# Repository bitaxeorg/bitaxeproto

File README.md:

bitaxeProto miner with quad Block Proto MC3 ASICs

It is still an untested prototype! Don't build this expecting it to work yet.

- [Open Hardware License](LICENSE); Real Open Source.
	- [KiCAD](https://kicad.org) design files. 
- Four Proto MC3 ASICs, two stacks of two ASICs
	- Each MC3 is nominally 1.12V with approx 675 GH/s.
- 11-13V XT30 input voltage
- TPS546D24S single-phase voltage regulator tuned for 2.4V output @ 30A
	- The voltage regulator backside power plane is exposed to hopefully thermally bond it with the main heatsink.
- TPS546D24 backside busbar to cool the voltage regulator from the main heatsink.
- Fan controlled from the ESP32
- ESP32S3 for [esp-miner](https://github.com/bitaxeorg/esp-miner) support.
- Display moved off the main board. Should support the [bonanzaDisplay](https://github.com/bitaxeorg/bonanzadisplay)
- Gerbers _not_ provided to discourage side hacks and AliEx slop. HMU if you need help generating gerbers with KiCad.

©️ [bitaxeorg](https://bitaxe.org)

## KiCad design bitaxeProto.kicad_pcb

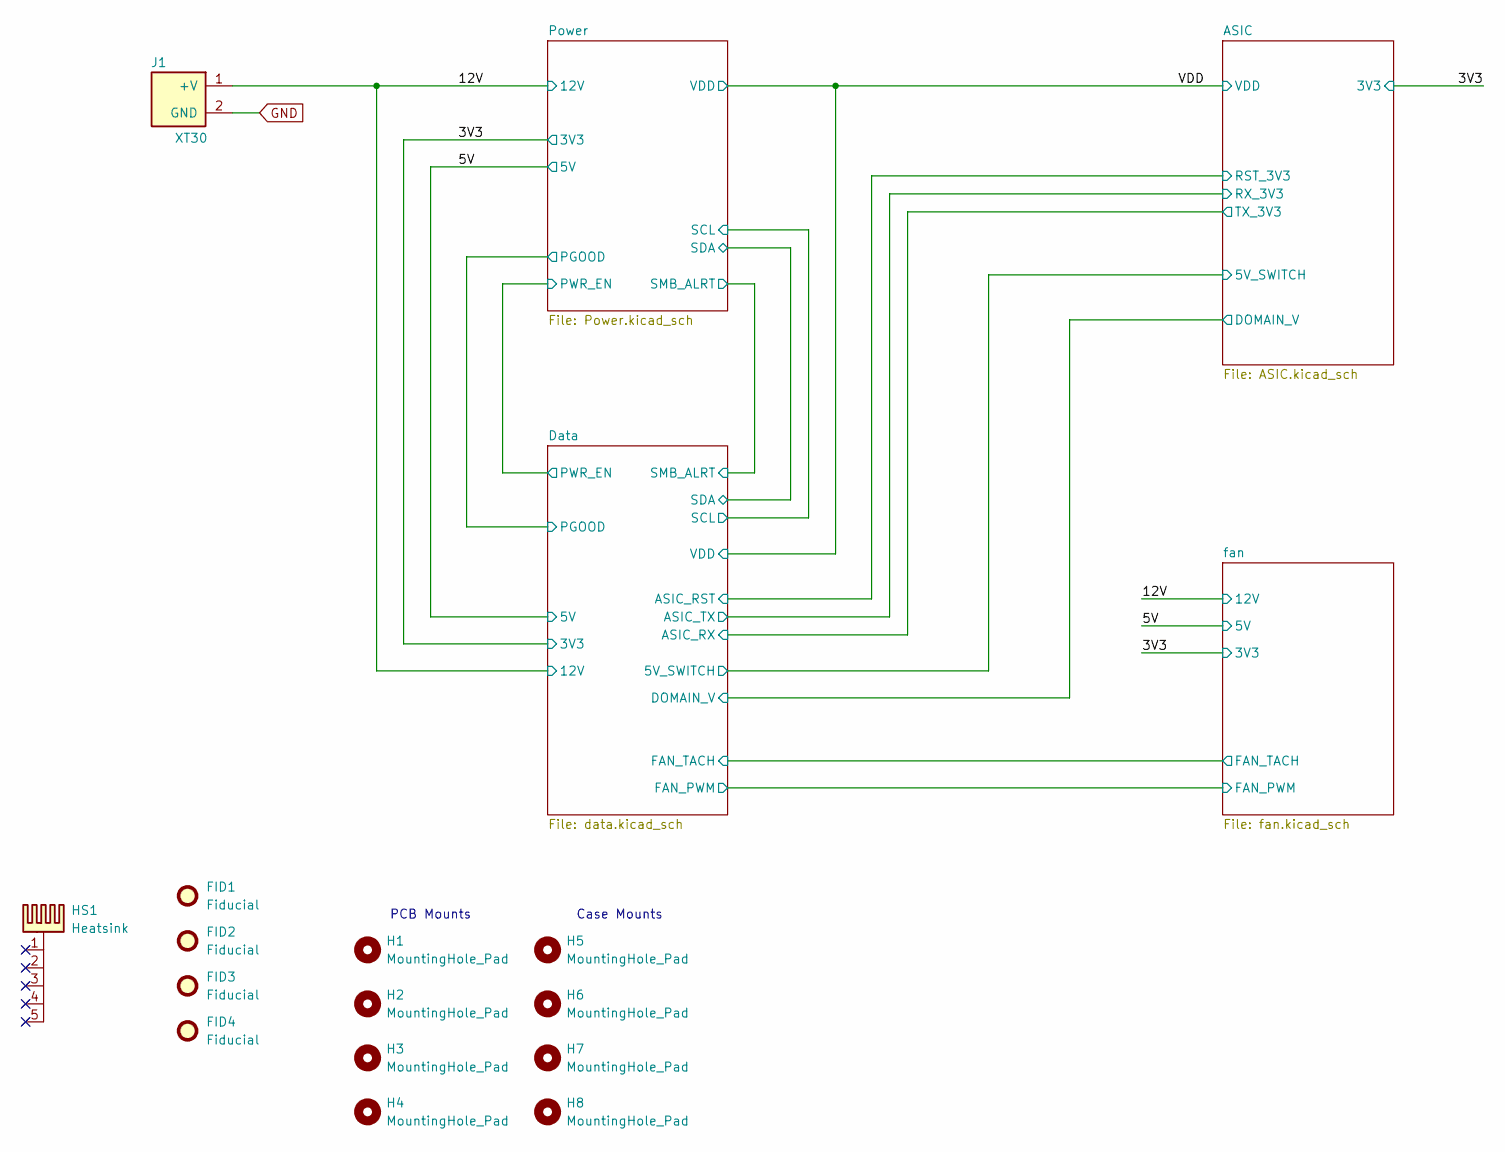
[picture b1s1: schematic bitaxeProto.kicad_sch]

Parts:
FID1, FID2, FID3, FID4: Fiducial; Fiducial_1mm_Mask2mm
H1, H2, H3, H4, H5, H6, H7, H8: MountingHole_Pad; MountingHole_3.2mm_M3
HS1: Heatsink; Heatsink-5hole-BitaxeGT
J1: XT30; XT30PW-M; PARTNO XT30PW-M30.G.Y; LCSC C431092

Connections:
/12V: J1.1 (+V); also elsewhere on the board
GND: J1.2 (GND); also elsewhere on the board

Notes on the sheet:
Case Mounts
PCB Mounts

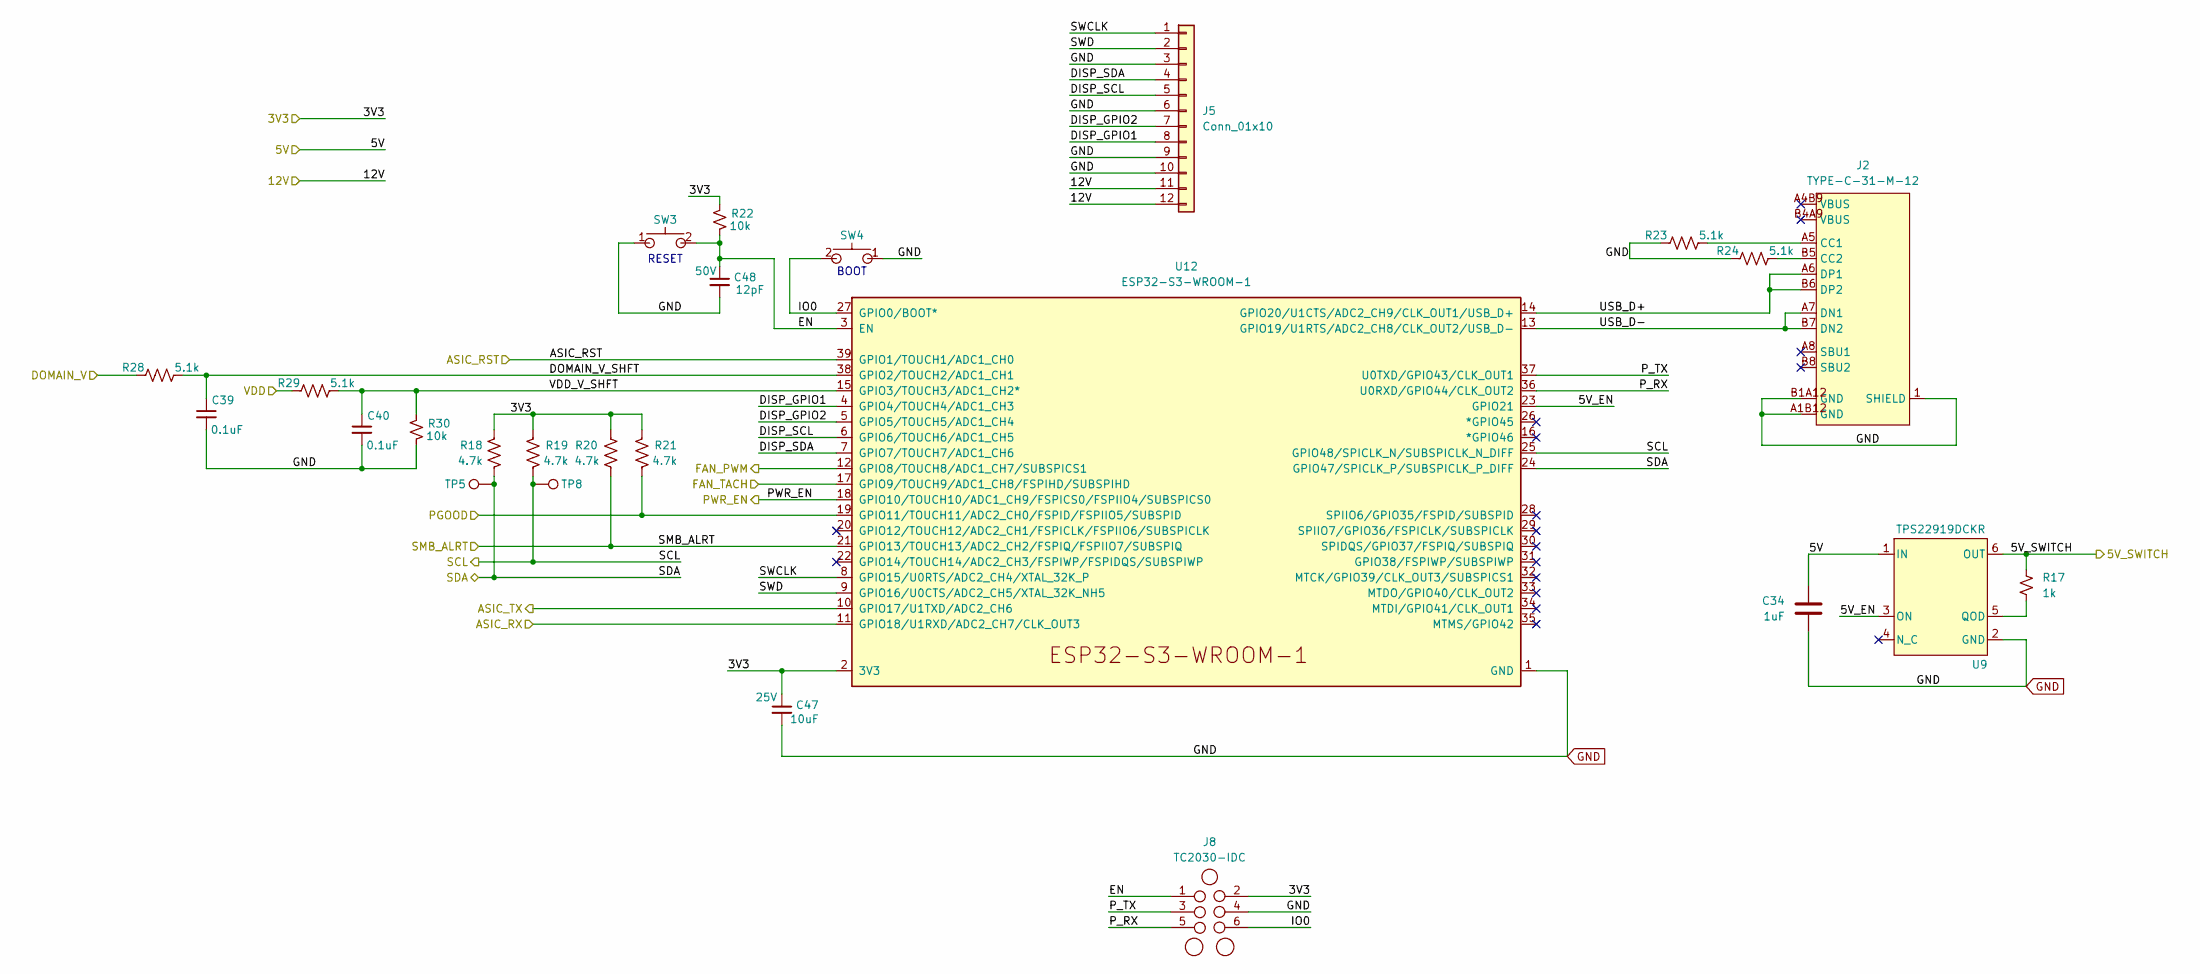
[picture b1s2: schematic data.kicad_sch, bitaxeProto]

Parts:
C34: 1uF; C_0402_1005Metric; PARTNO CL05A105KA5NQNC; LCSC C52923
C39, C40: 0.1uF; C_0402_1005Metric; Voltage 50V; PARTNO CL05B104KB54PNC; LCSC C307331
C47: 10uF; C_0603_1608Metric; Voltage 25V; PARTNO CL10A106MA8NRNC; LCSC C96446
C48: 12pF; C_0402_1005Metric; Voltage 50V; PARTNO 0402CG120J500NT; LCSC C1547
J2: TYPE-C-31-M-12; USB-C_SMD-TYPE-C-31-M-12_1; PARTNO TYPE-C-31-M-12; LCSC C165948
J5: Conn_01x10; CONN12_1-1735042-2; PARTNO 1-1735042-0
J8: TC2030-IDC; Tag-Connect_TC2030-IDC-NL_2x03_P1.27mm_Vertical
R17: 1k; R_0402_1005Metric; PARTNO 0402WGF1001TCE; LCSC C11702
R18, R19, R20, R21: 4.7k; R_0402_1005Metric; PARTNO 0402WGF4701TCE; LCSC C25900
R22, R30: 10k; R_0402_1005Metric; PARTNO 0402WGF1002TCE; LCSC C25744
R23, R24, R28, R29: 5.1k; R_0402_1005Metric; PARTNO 0402WGF5101TCE; LCSC C25905
SW3, SW4: SWITCH-SPST; SW-SMD_TC-S3601-3.5-260G-F0.6; PARTNO TC-S3601-3.5-260G-F0.6; LCSC C49101620
TP5: SDA; TestPoint_Pad_D1.0mm
TP8: SCL; TestPoint_Pad_D1.0mm
U9: TPS22919DCKR; DCK0006A_N; PARTNO TPS22919DCKR; LCSC C2149796
U12: ESP32-S3-WROOM-1; PARTNO ESP32-S3-WROOM-1-N16R8; LCSC C2913202

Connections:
/3V3: C47.1, J8.2, R18.1, R19.2, R20.2, R21.2, R22.2, U12.2 (3V3); also elsewhere on the board
/5V: C34.1, U9.1 (IN); also elsewhere on the board
/12V: J5.11, J5.12; also elsewhere on the board
/ASIC/5V_SWITCH: R17.1, U9.6 (OUT); also elsewhere on the board
/ASIC/GND0: R28.1; also elsewhere on the board
/ASIC/RX_3V3: U12.10 (GPIO17/U1TXD/ADC2_CH6); also elsewhere on the board
/ASIC/TX_3V3: U12.11 (GPIO18/U1RXD/ADC2_CH7/CLK_OUT3); also elsewhere on the board
/Data/5V_EN: U9.3 (ON), U12.23 (GPIO21)
/Data/ASIC_RST: U12.39 (GPIO1/TOUCH1/ADC1_CH0); also elsewhere on the board
/Data/DISP_GPIO1: J5.8, U12.4 (GPIO4/TOUCH4/ADC1_CH3)
/Data/DISP_GPIO2: J5.7, U12.5 (GPIO5/TOUCH5/ADC1_CH4)
/Data/DISP_SCL: J5.5, U12.6 (GPIO6/TOUCH6/ADC1_CH5)
/Data/DISP_SDA: J5.4, U12.7 (GPIO7/TOUCH7/ADC1_CH6)
/Data/DOMAIN_V_SHFT: C39.1, R28.2, U12.38 (GPIO2/TOUCH2/ADC1_CH1)
/Data/EN: C48.1, J8.1, R22.1, SW3.2, U12.3 (EN)
/Data/FAN_PWM: U12.12 (GPIO8/TOUCH8/ADC1_CH7/SUBSPICS1); also elsewhere on the board
/Data/FAN_TACH: U12.17 (GPIO9/TOUCH9/ADC1_CH8/FSPIHD/SUBSPIHD); also elsewhere on the board
/Data/IO0: J8.6, SW4.2, U12.27 (GPIO0/BOOT*)
/Data/PWR_EN: U12.18 (GPIO10/TOUCH10/ADC1_CH9/FSPICS0/FSPIIO4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); also elsewhere on the board
/Data/P_RX: J8.5, U12.36 (U0RXD/GPIO44/CLK_OUT2)
/Data/P_TX: J8.3, U12.37 (U0TXD/GPIO43/CLK_OUT1)
/Data/SCL: R19.1, TP8.1 (1_1), U12.25 (GPIO48/SPICLK_N/SUBSPICLK_N_DIFF); also elsewhere on the board
/Data/SDA: R18.2, TP5.1 (1_1), U12.24 (GPIO47/SPICLK_P/SUBSPICLK_P_DIFF); also elsewhere on the board
/Data/SMB_ALRT: R20.1, U12.21 (GPIO13/TOUCH13/ADC2_CH2/FSPIQ/FSPIIO7/S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); also elsewhere on the board
/Data/SWCLK: J5.1, U12.8 (GPIO15/U0RTS/ADC2_CH4/XTAL_32K_P)
/Data/SWD: J5.2, U12.9 (GPIO16/U0CTS/ADC2_CH5/XTAL_32K_NH5)
/Data/USB_D+: J2.A6 (DP1), J2.B6 (DP2), U12.14 (GPIO20/U1CTS/ADC2_CH9/CLK_OUT1/USB_D+)
/Data/USB_D-: J2.A7 (DN1), J2.B7 (DN2), U12.13 (GPIO19/U1RTS/ADC2_CH8/CLK_OUT2/USB_D-)
/Data/VDD_V_SHFT: C40.1, R29.2, R30.2, U12.15 (GPIO3/TOUCH3/ADC1_CH2*)
/Power/PGOOD: R21.1, U12.19 (GPIO11/TOUCH11/ADC2_CH0/FSPID/FSPIIO5/S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); also elsewhere on the board
/VDD: R29.1; also elsewhere on the board
GND: C34.2, C39.2, C40.2, C47.2, C48.2, J2.1 (SHIELD), J2.2 (EH), J2.3 (EH), J2.4 (EH), J2.A1B12 (GND), J2.B1A12 (GND), J5.3, J5.6, J5.9, J5.10, J8.4, R23.1, R24.1, R30.1, SW3.1, SW4.1, U9.2 (GND), U12.1 (GND), U12.40 (GND), U12.41 (GND); also elsewhere on the board
unnamed: J2.A5 (CC1), R23.2
unnamed: J2.B5 (CC2), R24.2
unnamed: R17.2, U9.5 (QOD)

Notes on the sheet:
BOOT
RESET

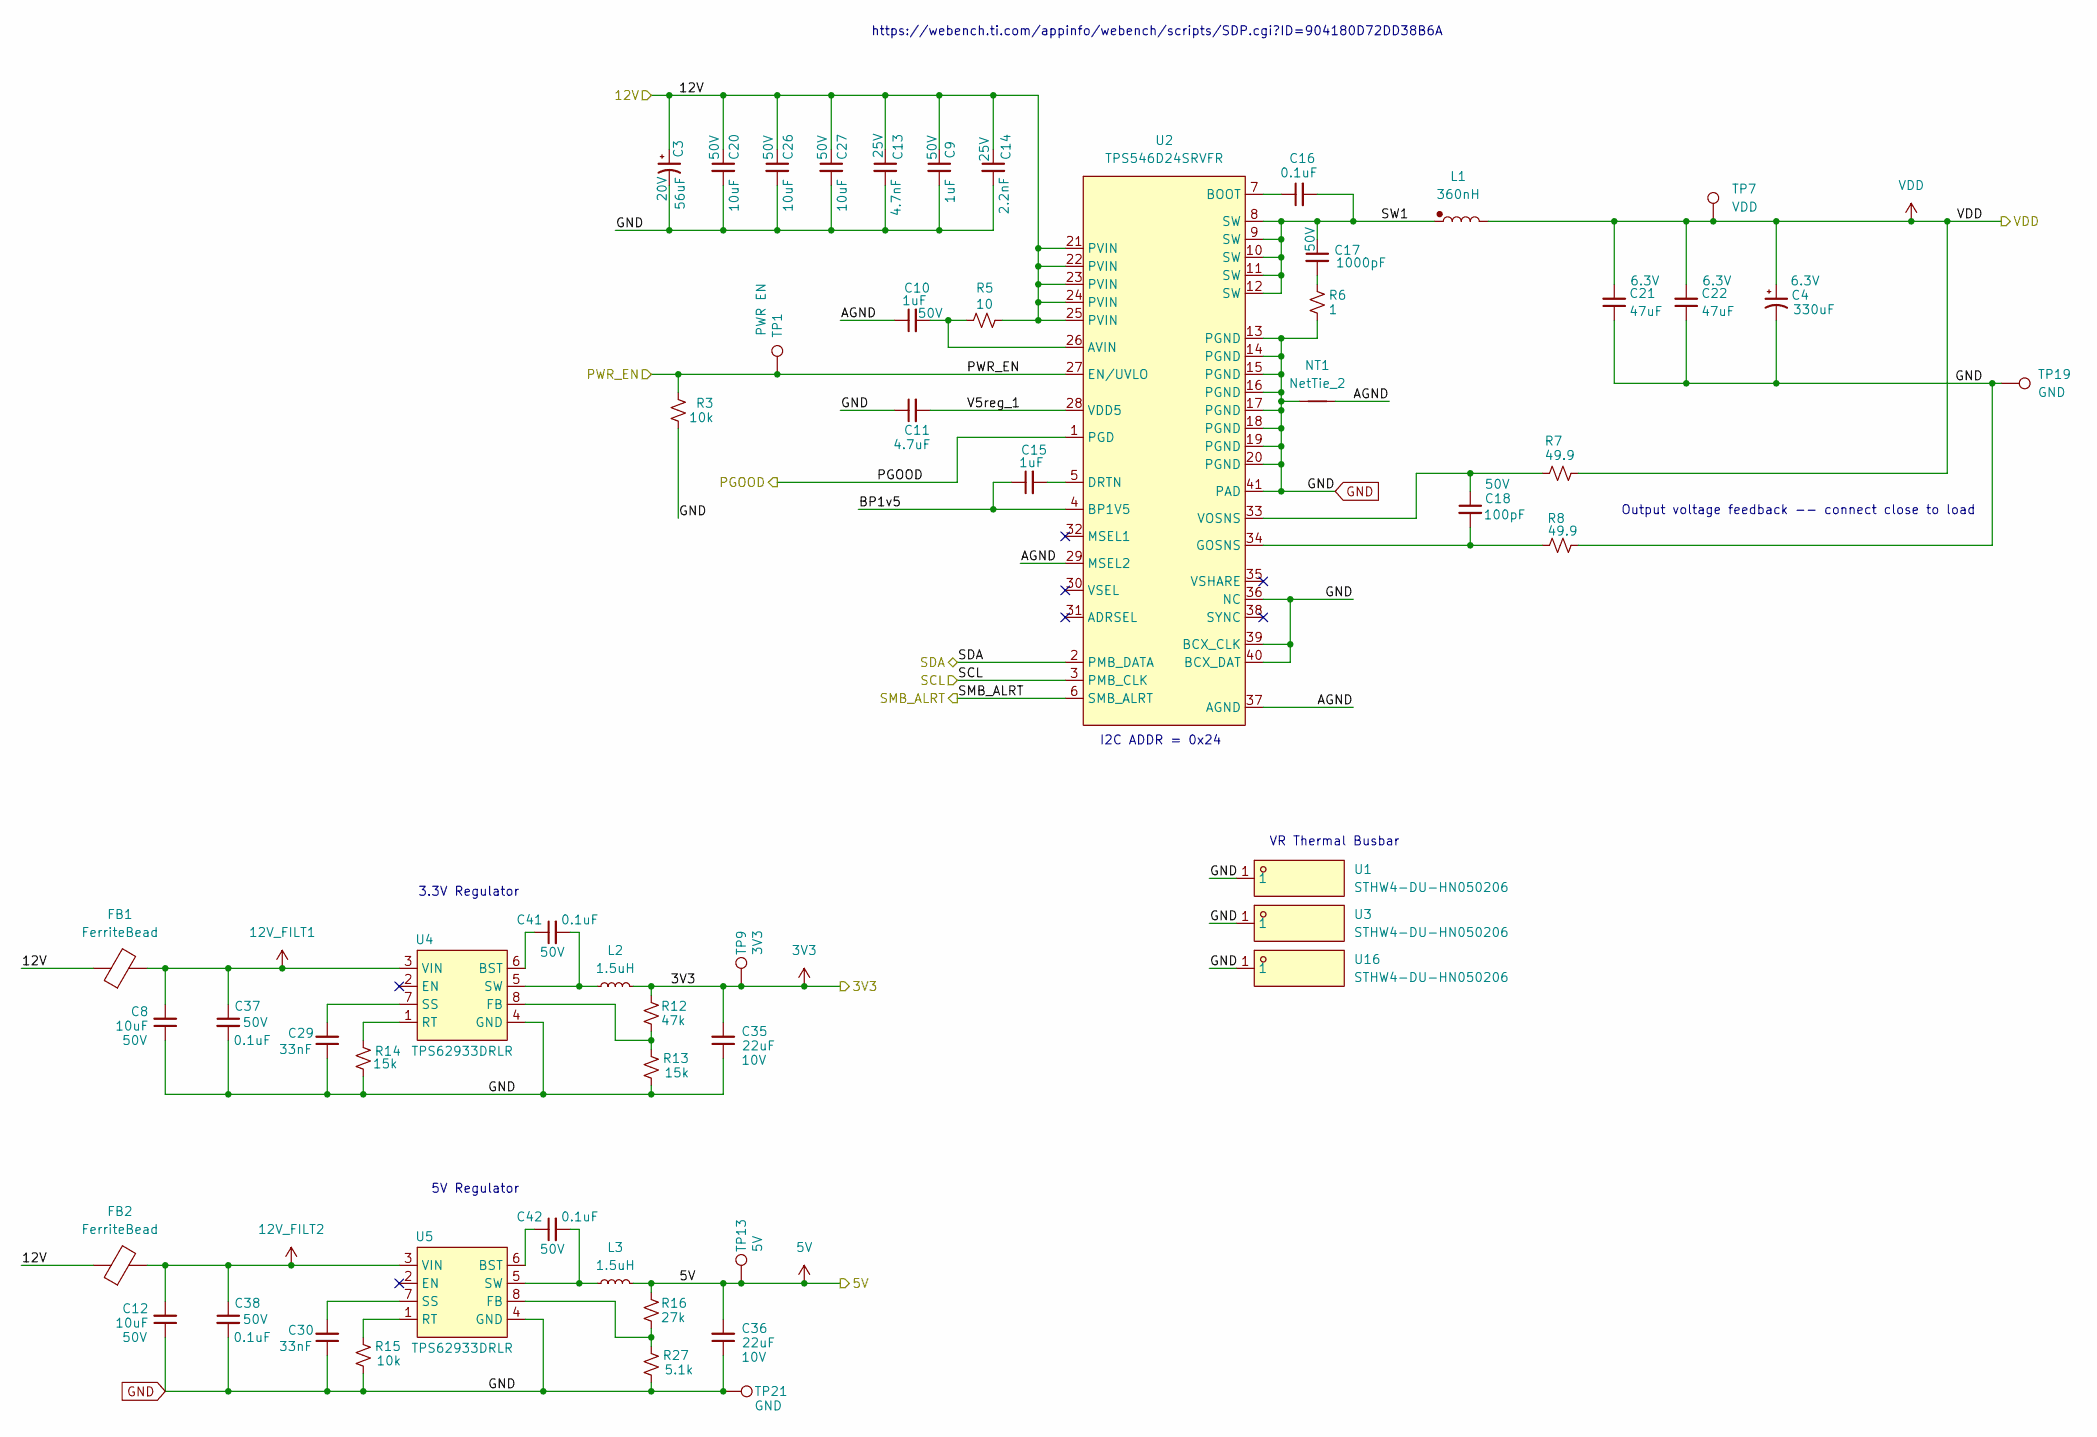
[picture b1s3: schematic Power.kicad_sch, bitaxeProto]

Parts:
C3: 56uF; CP_Elec_5x5.3; Voltage 20V; PARTNO 20SVPF56MX; LCSC C2162042
C4: 330uF; CP_Elec_6.3x7.7; Voltage 6.3V; PARTNO APXF6R3ARA331MF61G; LCSC C133476
C8, C12, C20, C26, C27: 10uF; C_1210_3225Metric; Voltage 50V; PARTNO CL32B106KBJNNNE; LCSC C138687
C9, C10: 1uF; C_0805_2012Metric; Voltage 50V; PARTNO CL21B105KBFNNNE; LCSC C28323
C11: 4.7uF; C_0402_1005Metric; PARTNO CL05A475MP5NRNC; LCSC C23733
C13: 4.7nF; C_0402_1005Metric; Voltage 25V; PARTNO 0402B472K500NT; LCSC C1538
C14: 2.2nF; C_0402_1005Metric; Voltage 25V; PARTNO 0402B222K500NT; LCSC C1531
C15: 1uF; C_0402_1005Metric; PARTNO CL05A105KA5NQNC; LCSC C52923
C16, C37, C38, C41, C42: 0.1uF; C_0402_1005Metric; Voltage 50V; PARTNO CL05B104KB54PNC; LCSC C307331
C17: 1000pF; C_0805_2012Metric; Voltage 50V; PARTNO CL21B102KBCNNNC; LCSC C46653
C18: 100pF; C_0402_1005Metric; Voltage 50V; PARTNO 0402CG101J500NT; LCSC C1546
C21, C22: 47uF; C_0805_2012Metric; Voltage 6.3V; PARTNO CL21A476MQYNNNE; LCSC C16780
C29, C30: 33nF; C_0603_1608Metric; PARTNO CL10B333KB8NNNC; LCSC C21117
C35, C36: 22uF; C_0805_2012Metric; Voltage 10V; PARTNO CL21A226MAQNNNE; LCSC C45783
FB1, FB2: FerriteBead; L_1206_3216Metric; PARTNO BLM31KN271SN1L; LCSC C703115
L1: 360nH; IND-SMD_L13.8-W12.6; PARTNO MS1350-R36M; LCSC C380062
L2, L3: 1.5uH; IND-SMD_L2.0-W1.6; PARTNO FTC201612S1R5MBCA; LCSC C5832350
NT1: NetTie_2; NetTie-2_SMD_Pad0.2mmx1mm
R3, R15: 10k; R_0402_1005Metric; PARTNO 0402WGF1002TCE; LCSC C25744
R5: 10; R_0402_1005Metric; PARTNO 0402WGF100JTCE; LCSC C25077
R6: 1; R_0805_2012Metric; PARTNO ESR10EZPJ1R0; LCSC C253344
R7, R8: 49.9; R_0402_1005Metric; PARTNO 0402WGF499JTCE; LCSC C25120
R12: 47k; R_0402_1005Metric; PARTNO 0402WGF4702TCE; LCSC C25792
R13, R14: 15k; R_0402_1005Metric; PARTNO 0402WGF1502TCE; LCSC C25756
R16: 27k; R_0402_1005Metric; PARTNO 0402WGF2702TCE; LCSC C25771
R27: 5.1k; R_0402_1005Metric; PARTNO 0402WGF5101TCE; LCSC C25905
TP1: PWR EN; TestPoint_Pad_D1.0mm
TP7: VDD; TestPoint_Pad_D1.0mm
TP9: 3V3; TestPoint_Pad_D1.0mm
TP13: 5V; TestPoint_Pad_D1.0mm
TP19, TP21: GND; TestPoint_Pad_D1.0mm
U1, U3, U16: STHW4-DU-HN050206; PAD-SMD_L5.0-W2.0_STHW4-DU-HN050206; PARTNO STHW4-DU-HN050206; LCSC C18548300
U2: TPS546D24SRVFR; LQFN40-CLIP; PARTNO TPS546D24SRVFR; LCSC C20345977
U4, U5: TPS62933DRLR; SOT-583-8_L2.1-W1.2-P0.50-LS1.6-BR; PARTNO TPS62933DRLR; LCSC C3200405

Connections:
/3V3: C35.2, L2.2, R12.2, TP9.1 (1_1); also elsewhere on the board
/5V: C36.2, L3.2, R16.2, TP13.1 (1_1); also elsewhere on the board
/12V: C3.1, C9.1, C13.1, C14.1, C20.1, C26.1, C27.1, FB1.1, FB2.1, R5.1, U2.21 (PVIN), U2.22 (PVIN), U2.23 (PVIN), U2.24 (PVIN), U2.25 (PVIN); also elsewhere on the board
/Data/PWR_EN: R3.2, TP1.1 (1_1), U2.27 (EN/UVLO); also elsewhere on the board
/Data/SCL: U2.3 (PMB_CLK); also elsewhere on the board
/Data/SDA: U2.2 (PMB_DATA); also elsewhere on the board
/Data/SMB_ALRT: U2.6 (SMB_ALRT); also elsewhere on the board
/Power/AGND: C10.1, NT1.2, U2.29 (MSEL2), U2.37 (AGND)
/Power/BP1v5: C15.1, U2.4 (BP1V5)
/Power/PGOOD: U2.1 (PGD); also elsewhere on the board
/Power/SW1: C16.2, C17.1, L1.1, U2.8 (SW), U2.9 (SW), U2.10 (SW), U2.11 (SW), U2.12 (SW)
/Power/V5reg_1: C11.2, U2.28 (VDD5)
/VDD: C4.1, C21.2, C22.2, L1.2, R7.1, TP7.1 (1_1); also elsewhere on the board
GND: C3.2, C4.2, C8.1, C9.2, C11.1, C12.1, C13.2, C14.2, C20.2, C21.1, C22.1, C26.2, C27.2, C29.1, C30.1, C35.1, C36.1, C37.2, C38.2, NT1.1, R3.1, R6.2, R8.2, R13.1, R14.1, R15.1, R27.1, TP19.1 (1_1), TP21.1 (1_1), U1.1 (1_1), U2.13 (PGND), U2.14 (PGND), U2.15 (PGND), U2.16 (PGND), U2.17 (PGND), U2.18 (PGND), U2.19 (PGND), U2.20 (PGND), U2.36 (NC), U2.39 (BCX_CLK), U2.40 (BCX_DAT), U2.41 (PAD), U3.1 (1_1), U4.4 (GND), U5.4 (GND), U16.1 (1_1); also elsewhere on the board
unnamed: C17.2, R6.1
unnamed: C10.2, R5.2, U2.26 (AVIN)
unnamed: C16.1, U2.7 (BOOT)
unnamed: C15.2, U2.5 (DRTN)
unnamed: C18.2, R8.1, U2.34 (GOSNS)
unnamed: C18.1, R7.2, U2.33 (VOSNS)
unnamed: C41.1, U4.6 (BST)
unnamed: R12.1, R13.2, U4.8 (FB)
unnamed: R14.2, U4.1 (RT)
unnamed: C29.2, U4.7 (SS)
unnamed: C41.2, L2.1, U4.5 (SW)
unnamed: C8.2, C37.1, FB1.2, U4.3 (VIN)
unnamed: C42.1, U5.6 (BST)
unnamed: R16.1, R27.2, U5.8 (FB)
unnamed: R15.2, U5.1 (RT)
unnamed: C30.2, U5.7 (SS)
unnamed: C42.2, L3.1, U5.5 (SW)
unnamed: C12.2, C38.1, FB2.2, U5.3 (VIN)

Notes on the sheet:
I2C ADDR = 0x24
3.3V Regulator
VR Thermal Busbar
5V Regulator
Output voltage feedback -- connect close to load
https://webench.ti.com/appinfo/webench/scripts/SDP.cgi?ID=904180D72DD38B6A

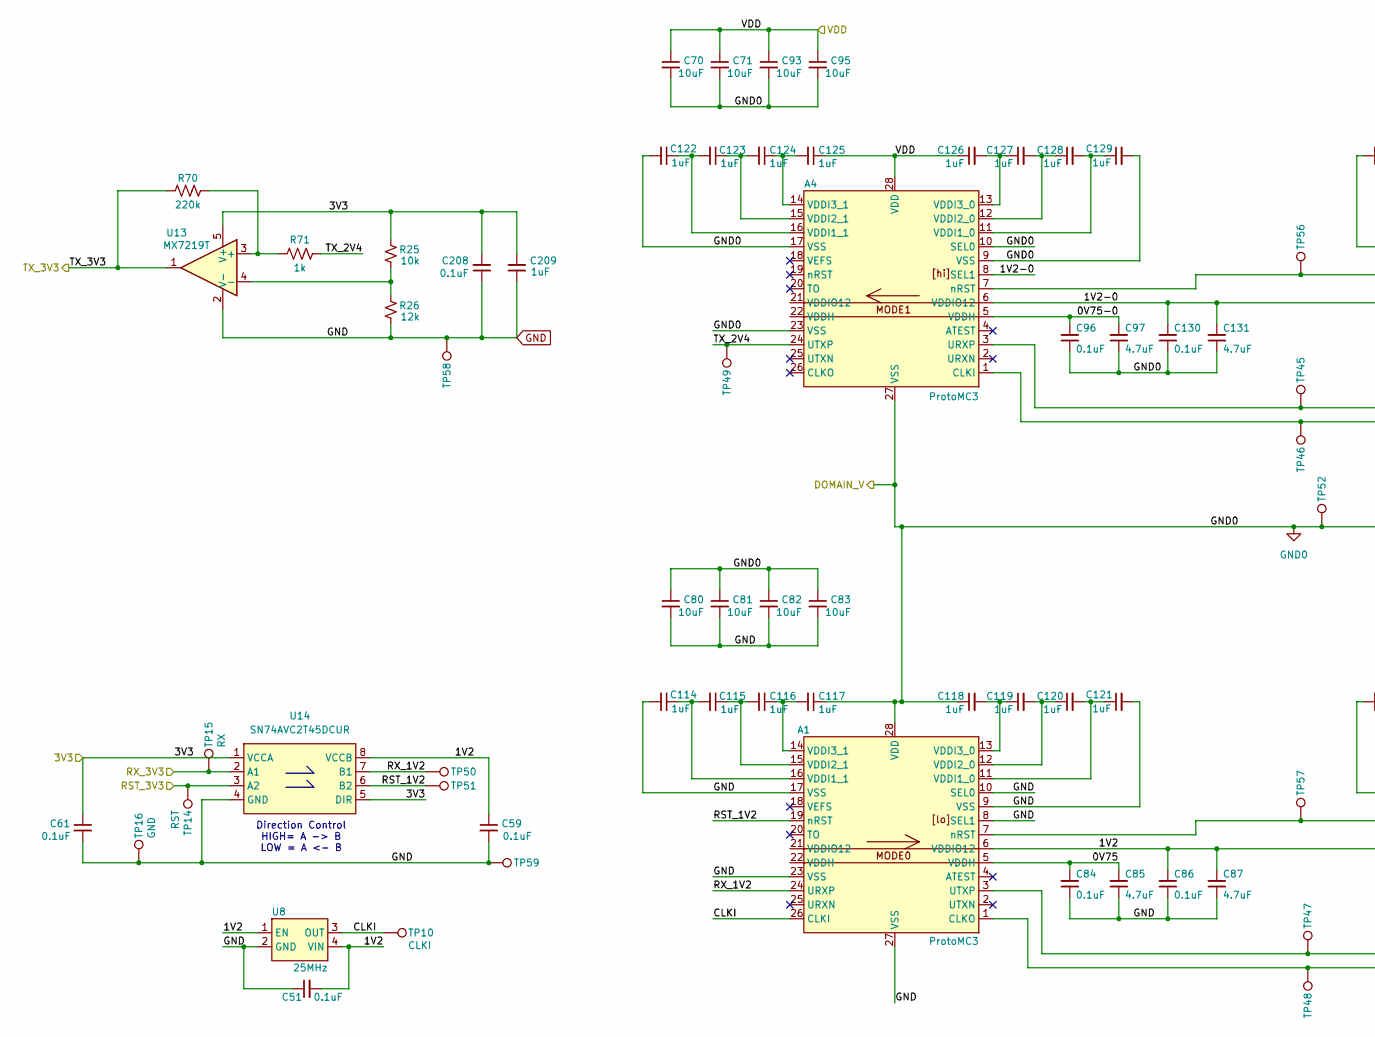
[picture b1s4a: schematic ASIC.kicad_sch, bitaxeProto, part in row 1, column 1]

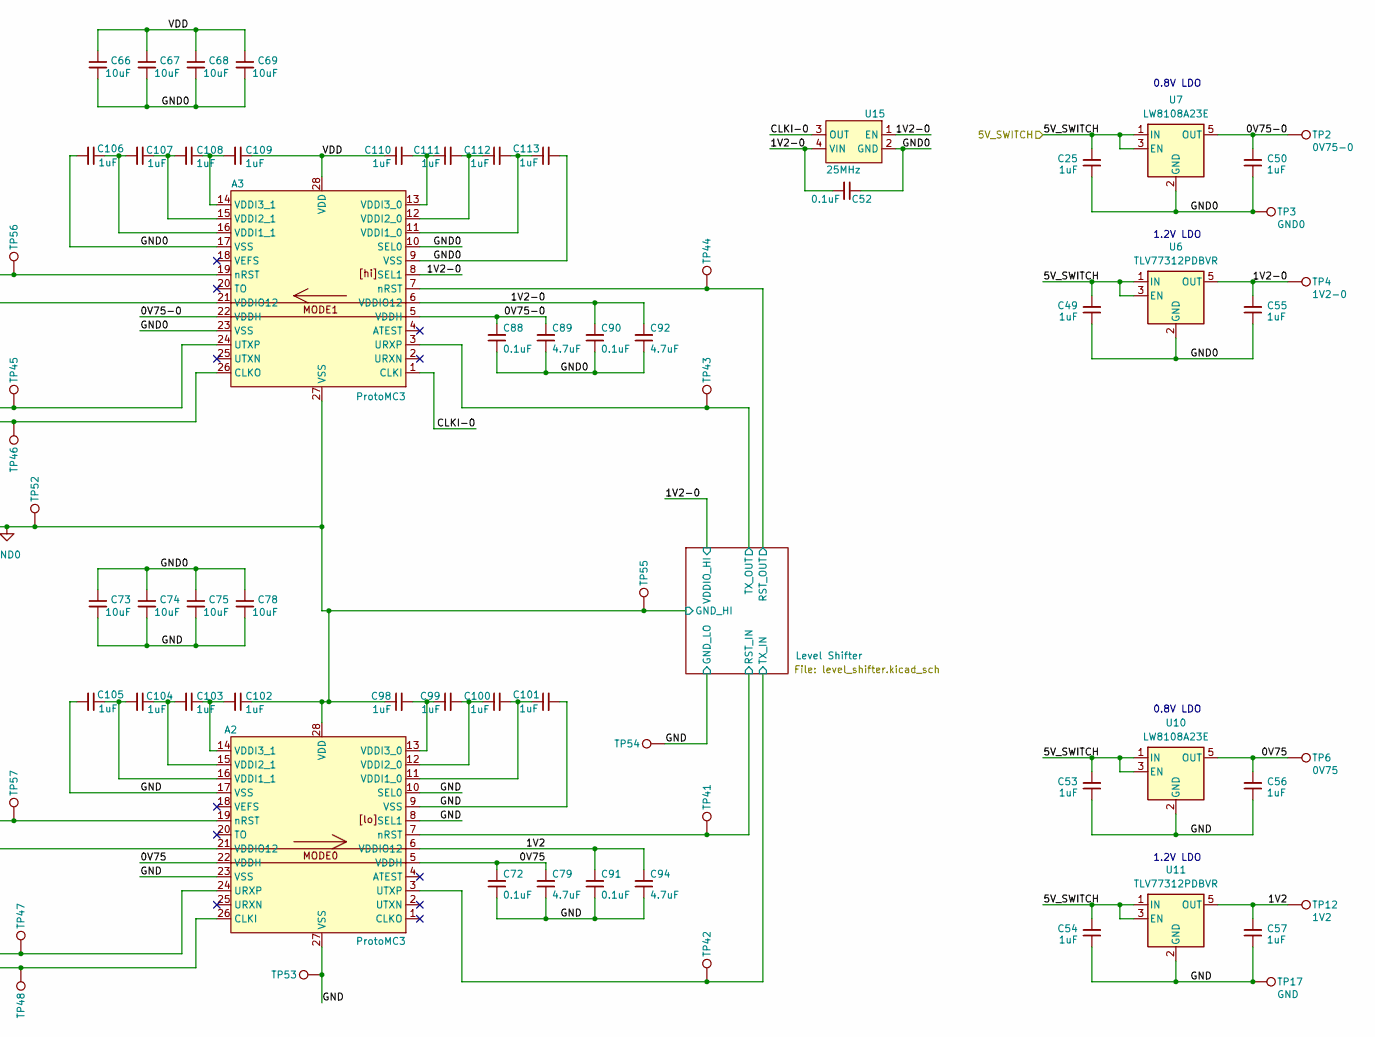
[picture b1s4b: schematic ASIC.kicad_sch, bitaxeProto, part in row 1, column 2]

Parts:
A1, A2, A3, A4: ProtoMC3; proto-mc3
C25, C49, C50, C53, C54, C55, C56, C57, C98, C99, C100, C101, C102, C103, C104, C105, C106, C107, C108, C109, C110, C111, C112, C113, C114, C115, C116, C117, C118, C119, C120, C121, C122, C123, C124, C125, C126, C127, C128, C129, C209: 1uF; C_0402_1005Metric; PARTNO CL05A105KA5NQNC; LCSC C52923
C51, C52, C59, C61, C72, C84, C86, C88, C90, C91, C96, C130, C208: 0.1uF; C_0402_1005Metric; Voltage 50V; PARTNO CL05B104KB54PNC; LCSC C307331
C66, C67, C68, C69, C70, C71, C73, C74, C75, C78, C80, C81, C82, C83, C93, C95: 10uF; C_0603_1608Metric; Voltage 25V; PARTNO CL10A106MA8NRNC; LCSC C96446
C79, C85, C87, C89, C92, C94, C97, C131: 4.7uF; C_0402_1005Metric; PARTNO CL05A475MP5NRNC; LCSC C23733
R25: 10k; R_0402_1005Metric; PARTNO 0402WGF1002TCE; LCSC C25744
R26: 12k; R_0402_1005Metric; PARTNO 0402WGF1202TCE; LCSC C25752
R70: 220k; R_0402_1005Metric; PARTNO RC0402FR-07220KL; LCSC C138030
R71: 1k; R_0402_1005Metric; PARTNO 0402WGF1001TCE; LCSC C11702
TP2: 0V75-0; TestPoint_Pad_D1.0mm
TP3: GND0; TestPoint_Pad_D1.0mm
TP4: 1V2-0; TestPoint_Pad_D1.0mm
TP6: 0V75; TestPoint_Pad_D1.0mm
TP10: CLKI; TestPoint_Pad_D1.0mm
TP12: 1V2; TestPoint_Pad_D1.0mm
TP14: RST; TestPoint_Pad_D1.0mm
TP15: RX; TestPoint_Pad_D1.0mm
TP16, TP17: GND; TestPoint_Pad_D1.0mm
TP41, TP44, TP51, TP56, TP57: RST; TestPoint_Pad_1.0x0.4mm
TP42, TP49: TX; TestPoint_Pad_1.0x0.4mm
TP43, TP45, TP47, TP50: RX; TestPoint_Pad_1.0x0.4mm
TP46, TP48: CLK; TestPoint_Pad_1.0x0.4mm
TP52, TP53, TP54, TP55, TP58, TP59: GND; TestPoint_Pad_1.0x0.4mm
U6, U11: TLV77312PDBVR; SOT-23-5; PARTNO TLV77312PDBVR; LCSC C30806341
U7, U10: LW8108A23E; SOT-23-5; PARTNO LW8108A23E; LCSC C51953196
U8, U15: 25MHz; SMD3225-4P; PARTNO SX3M25.000E20F30THN; LCSC C5137262
U13: MX7219T; SOT-23-5; PARTNO MX7219T; LCSC C20882980
U14: SN74AVC2T45DCUR; VSSOP-8_L2.1-W2.4-P0.50-LS3.2-BR; PARTNO SN74AVC2T45DCUR; LCSC C140318

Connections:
/3V3: C61.1, C208.2, C209.2, R25.2, U13.5 (V+), U14.1 (VCCA), U14.5 (DIR); also elsewhere on the board
/ASIC/0V75: A1.5 (VDDH), A1.22 (VDDH), A2.5 (VDDH), A2.22 (VDDH), C56.2, C72.2, C79.2, C84.2, C85.2, TP6.1 (1_1), U10.5 (OUT)
/ASIC/0V75-0: A3.5 (VDDH), A3.22 (VDDH), A4.5 (VDDH), A4.22 (VDDH), C50.2, C88.2, C89.2, C96.2, C97.2, TP2.1 (1_1), U7.5 (OUT)
/ASIC/1V2: A1.6 (VDDIO12), A1.21 (VDDIO12), A2.6 (VDDIO12), A2.21 (VDDIO12), C51.2, C57.2, C59.1, C86.2, C87.2, C91.2, C94.2, TP12.1 (1_1), U8.1 (EN), U8.4 (VIN), U11.5 (OUT), U14.8 (VCCB)
/ASIC/1V2-0: A3.6 (VDDIO12), A3.8 (SEL1), A3.21 (VDDIO12), A4.6 (VDDIO12), A4.8 (SEL1), A4.21 (VDDIO12), C52.2, C55.2, C90.2, C92.2, C130.2, C131.2, TP4.1 (1_1), U6.5 (OUT), U15.1 (EN), U15.4 (VIN); also elsewhere on the board
/ASIC/5V_SWITCH: C25.2, C49.2, C53.2, C54.2, U6.1 (IN), U6.3 (EN), U7.1 (IN), U7.3 (EN), U10.1 (IN), U10.3 (EN), U11.1 (IN), U11.3 (EN); also elsewhere on the board
/ASIC/CLKI: A1.26 (CLKI), TP10.1 (1_1), U8.3 (OUT)
/ASIC/CLKI-0: A3.1 (CLKI), U15.3 (OUT)
/ASIC/GND0: A1.28 (VDD), A2.28 (VDD), A3.9 (VSS), A3.10 (SEL0), A3.17 (VSS), A3.23 (VSS), A3.27 (VSS), A4.9 (VSS), A4.10 (SEL0), A4.17 (VSS), A4.23 (VSS), A4.27 (VSS), C25.1, C49.1, C50.1, C52.1, C55.1, C66.2, C67.2, C68.2, C69.2, C70.2, C71.2, C73.1, C74.1, C75.1, C78.1, C80.1, C81.1, C82.1, C83.1, C88.1, C89.1, C90.1, C92.1, C93.2, C95.2, C96.1, C97.1, C98.1, C102.1, C106.2, C113.2, C117.1, C118.1, C122.2, C129.2, C130.1, C131.1, TP3.1 (1_1), TP52.1 (1_1), TP55.1 (1_1), U6.2 (GND), U7.2 (GND), U15.2 (GND); also elsewhere on the board
/ASIC/Level Shifter/RST_IN: A2.7 (nRST), TP41.1 (1_1); also elsewhere on the board
/ASIC/Level Shifter/RST_OUT: A3.7 (nRST), TP44.1 (1_1); also elsewhere on the board
/ASIC/Level Shifter/TX_IN: A2.3 (UTXP), TP42.1 (1_1); also elsewhere on the board
/ASIC/Level Shifter/TX_OUT: A3.3 (URXP), TP43.1 (1_1); also elsewhere on the board
/ASIC/RST_1V2: A1.19 (nRST), TP51.1 (1_1), U14.6 (B2)
/ASIC/RX_1V2: A1.24 (URXP), TP50.1 (1_1), U14.7 (B1)
/ASIC/RX_3V3: TP15.1 (1_1), U14.2 (A1); also elsewhere on the board
/ASIC/TX_2V4: A4.24 (UTXP), R71.1, TP49.1 (1_1)
/ASIC/TX_3V3: R70.2, U13.1; also elsewhere on the board
/Data/ASIC_RST: TP14.1 (1_1), U14.3 (A2); also elsewhere on the board
/VDD: A3.28 (VDD), A4.28 (VDD), C66.1, C67.1, C68.1, C69.1, C70.1, C71.1, C93.1, C95.1, C109.1, C110.1, C125.1, C126.1; also elsewhere on the board
GND: A1.8 (SEL1), A1.9 (VSS), A1.10 (SEL0), A1.17 (VSS), A1.23 (VSS), A1.27 (VSS), A2.8 (SEL1), A2.9 (VSS), A2.10 (SEL0), A2.17 (VSS), A2.23 (VSS), A2.27 (VSS), C51.1, C53.1, C54.1, C56.1, C57.1, C59.2, C61.2, C72.1, C73.2, C74.2, C75.2, C78.2, C79.1, C80.2, C81.2, C82.2, C83.2, C84.1, C85.1, C86.1, C87.1, C91.1, C94.1, C101.2, C105.2, C114.2, C121.2, C208.1, C209.1, R26.1, TP16.1 (1_1), TP17.1 (1_1), TP53.1 (1_1), TP54.1 (1_1), TP58.1 (1_1), TP59.1 (1_1), U8.2 (GND), U10.2 (GND), U11.2 (GND), U13.2 (V-), U14.4 (GND); also elsewhere on the board
unnamed: A1.1 (CLKO), A2.26 (CLKI), TP48.1 (1_1)
unnamed: A1.3 (UTXP), A2.24 (URXP), TP47.1 (1_1)
unnamed: A1.11 (VDDI1_0), C120.2, C121.1
unnamed: A1.16 (VDDI1_1), C114.1, C115.2
unnamed: A1.12 (VDDI2_0), C119.2, C120.1
unnamed: A1.15 (VDDI2_1), C115.1, C116.2
unnamed: A1.13 (VDDI3_0), C118.2, C119.1
unnamed: A1.14 (VDDI3_1), C116.1, C117.2
unnamed: A1.7 (nRST), A2.19 (nRST), TP57.1 (1_1)
unnamed: A2.11 (VDDI1_0), C100.2, C101.1
unnamed: A2.16 (VDDI1_1), C104.2, C105.1
unnamed: A2.12 (VDDI2_0), C99.2, C100.1
unnamed: A2.15 (VDDI2_1), C103.2, C104.1
unnamed: A2.13 (VDDI3_0), C98.2, C99.1
unnamed: A2.14 (VDDI3_1), C102.2, C103.1
unnamed: A3.26 (CLKO), A4.1 (CLKI), TP46.1 (1_1)
unnamed: A3.24 (UTXP), A4.3 (URXP), TP45.1 (1_1)
unnamed: A3.11 (VDDI1_0), C112.2, C113.1
unnamed: A3.16 (VDDI1_1), C106.1, C107.2
unnamed: A3.12 (VDDI2_0), C111.2, C112.1
unnamed: A3.15 (VDDI2_1), C107.1, C108.2
unnamed: A3.13 (VDDI3_0), C110.2, C111.1
unnamed: A3.14 (VDDI3_1), C108.1, C109.2
unnamed: A3.19 (nRST), A4.7 (nRST), TP56.1 (1_1)
unnamed: A4.11 (VDDI1_0), C128.2, C129.1
unnamed: A4.16 (VDDI1_1), C122.1, C123.2
unnamed: A4.12 (VDDI2_0), C127.2, C128.1
unnamed: A4.15 (VDDI2_1), C123.1, C124.2
unnamed: A4.13 (VDDI3_0), C126.2, C127.1
unnamed: A4.14 (VDDI3_1), C124.1, C125.2
unnamed: R70.1, R71.2, U13.3 (+)
unnamed: R25.1, R26.2, U13.4 (-)

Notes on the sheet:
1.2V LDO
Direction Control HIGH= A -> B LOW = A <- B
0.8V LDO

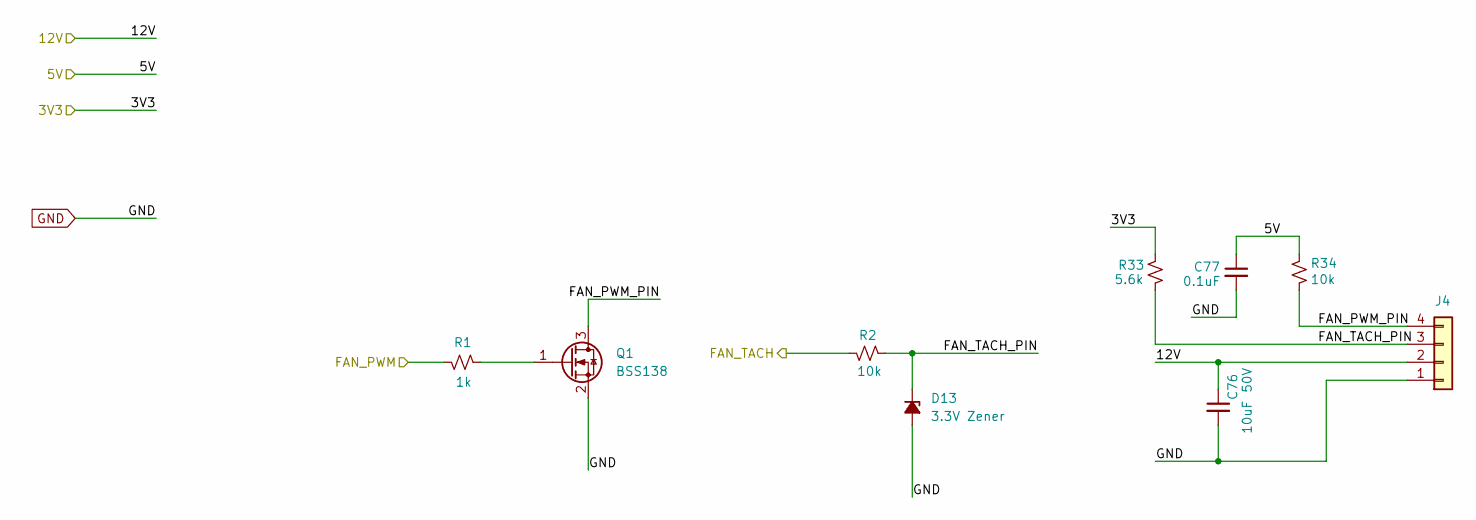
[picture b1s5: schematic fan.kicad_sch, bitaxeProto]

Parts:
C76: 10uF; C_1210_3225Metric; Voltage 50V; PARTNO CL32B106KBJNNNE; LCSC C138687
C77: 0.1uF; C_0402_1005Metric; Voltage 50V; PARTNO CL05B104KB54PNC; LCSC C307331
D13: 3.3V Zener; D_SOD-123; PARTNO MMSZ4684T1G; LCSC C24672
J4: Conn_01x04; fan_connector; PARTNO 0470531000
Q1: BSS138; SOT-23; PARTNO BSS138; LCSC C7420339
R1: 1k; R_0402_1005Metric; PARTNO 0402WGF1001TCE; LCSC C11702
R2, R34: 10k; R_0402_1005Metric; PARTNO 0402WGF1002TCE; LCSC C25744
R33: 5.6k; R_0402_1005Metric; PARTNO 0402WGF5601TCE; LCSC C25908

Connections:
/3V3: R33.2; also elsewhere on the board
/5V: C77.1, R34.2; also elsewhere on the board
/12V: C76.1, J4.2; also elsewhere on the board
/Data/FAN_PWM: R1.2; also elsewhere on the board
/Data/FAN_TACH: R2.2; also elsewhere on the board
/fan/FAN_PWM_PIN: J4.4, Q1.3 (D), R34.1
/fan/FAN_TACH_PIN: D13.1 (K), J4.3, R2.1, R33.1
GND: C76.2, C77.2, D13.2 (A), J4.1, Q1.2 (S); also elsewhere on the board
unnamed: Q1.1 (G), R1.1

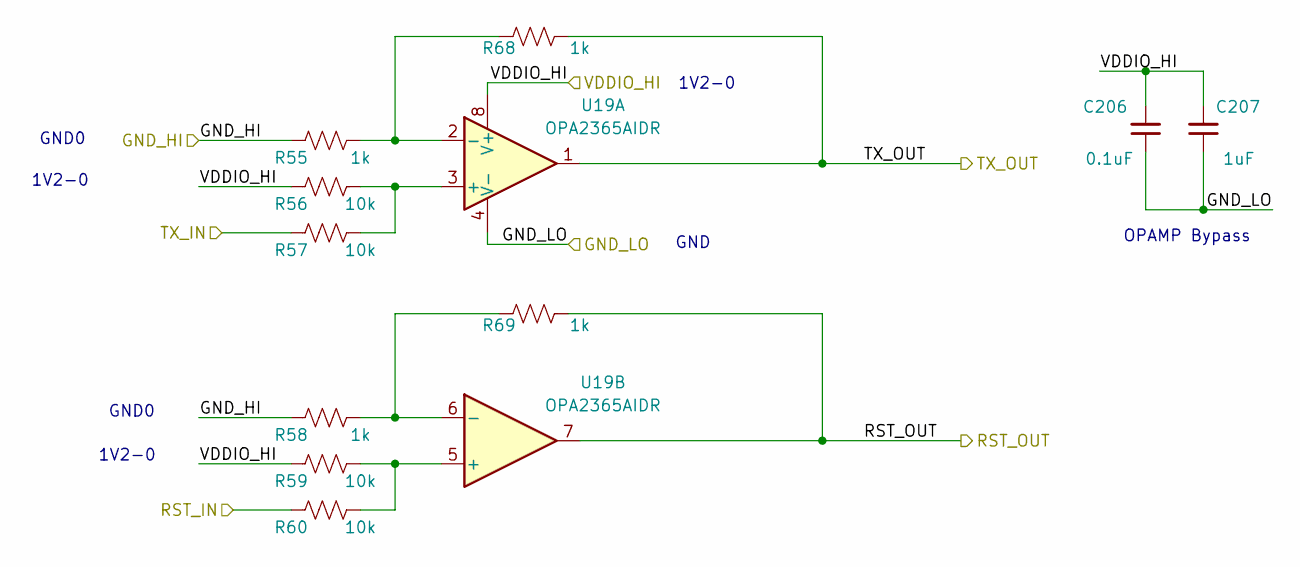
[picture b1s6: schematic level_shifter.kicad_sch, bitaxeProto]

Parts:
C206: 0.1uF; C_0402_1005Metric; Voltage 50V; PARTNO CL05B104KB54PNC; LCSC C307331
C207: 1uF; C_0402_1005Metric; PARTNO CL05A105KA5NQNC; LCSC C52923
R55, R58, R68, R69: 1k; R_0402_1005Metric; PARTNO 0402WGF1001TCE; LCSC C11702
R56, R57, R59, R60: 10k; R_0402_1005Metric; PARTNO 0402WGF1002TCE; LCSC C25744
U19: OPA2365AIDR; D8_TEX; PARTNO OPA2365AIDR; LCSC C130011

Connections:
/ASIC/1V2-0: C206.2, C207.2, R56.2, R59.1, U19.8 (V+); also elsewhere on the board
/ASIC/GND0: R55.2, R58.2; also elsewhere on the board
/ASIC/Level Shifter/RST_IN: R60.1; also elsewhere on the board
/ASIC/Level Shifter/RST_OUT: R69.1, U19.7; also elsewhere on the board
/ASIC/Level Shifter/TX_IN: R57.1; also elsewhere on the board
/ASIC/Level Shifter/TX_OUT: R68.1, U19.1; also elsewhere on the board
GND: C206.1, C207.1, U19.4 (V-); also elsewhere on the board
unnamed: R56.1, R57.2, U19.3 (+)
unnamed: R55.1, R68.2, U19.2 (-)
unnamed: R59.2, R60.2, U19.5 (+)
unnamed: R58.1, R69.2, U19.6 (-)

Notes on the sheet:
1V2-0
GND0
GND
OPAMP Bypass
